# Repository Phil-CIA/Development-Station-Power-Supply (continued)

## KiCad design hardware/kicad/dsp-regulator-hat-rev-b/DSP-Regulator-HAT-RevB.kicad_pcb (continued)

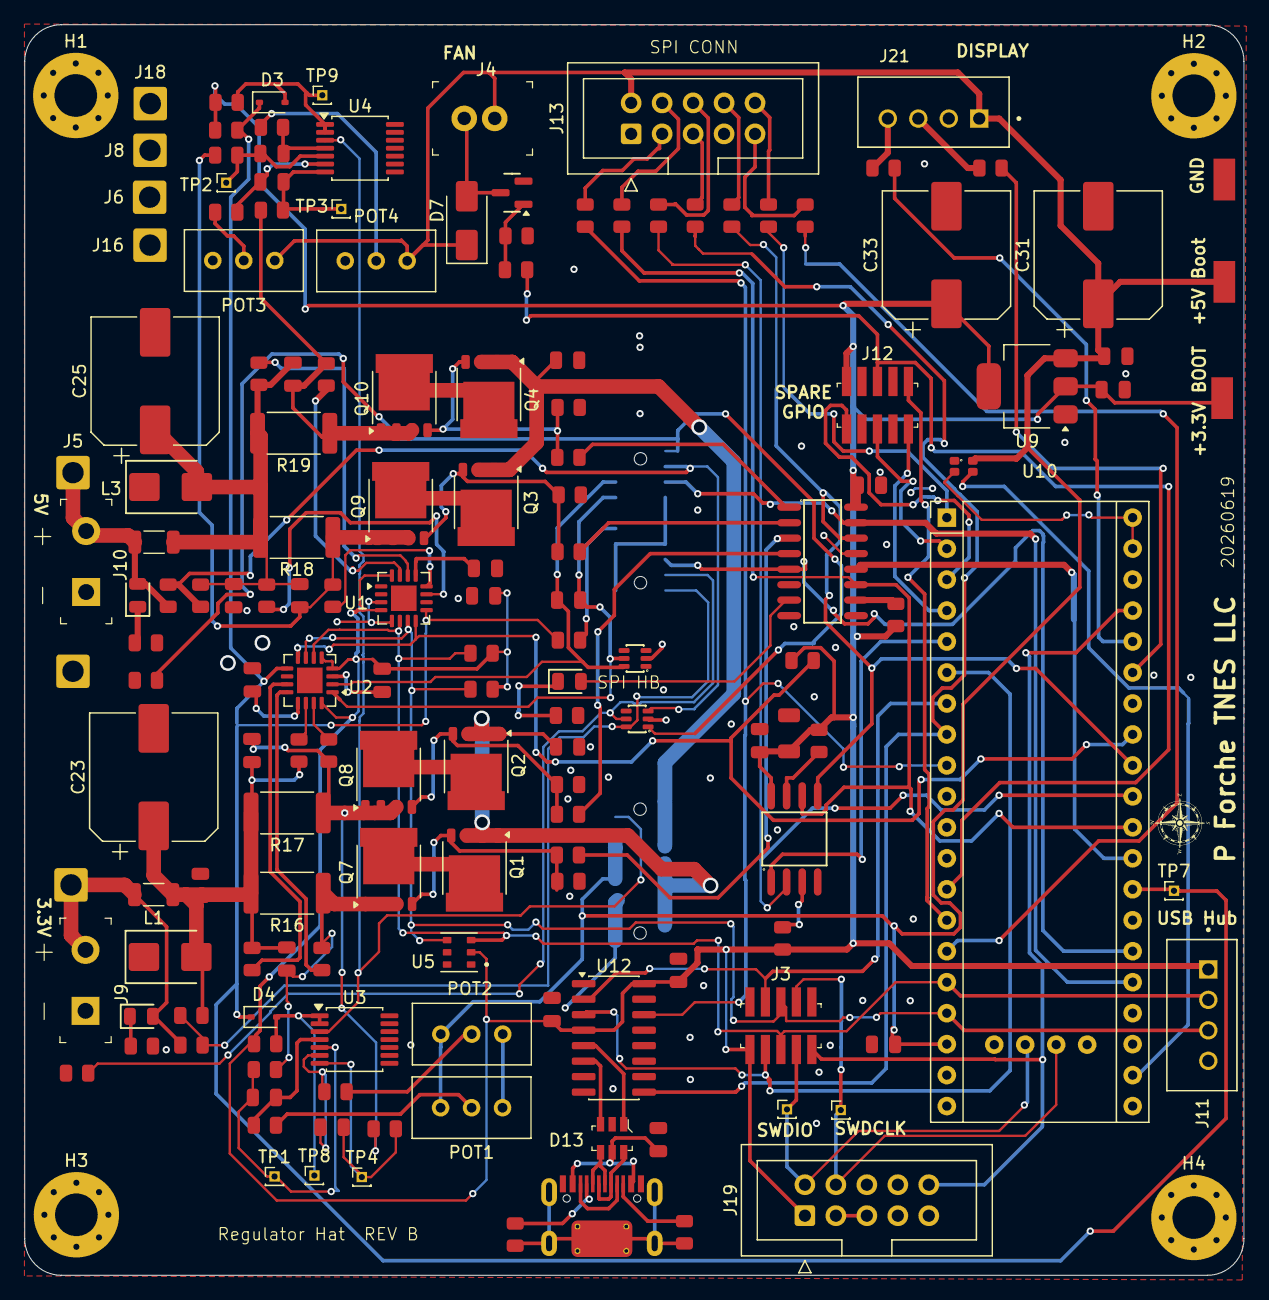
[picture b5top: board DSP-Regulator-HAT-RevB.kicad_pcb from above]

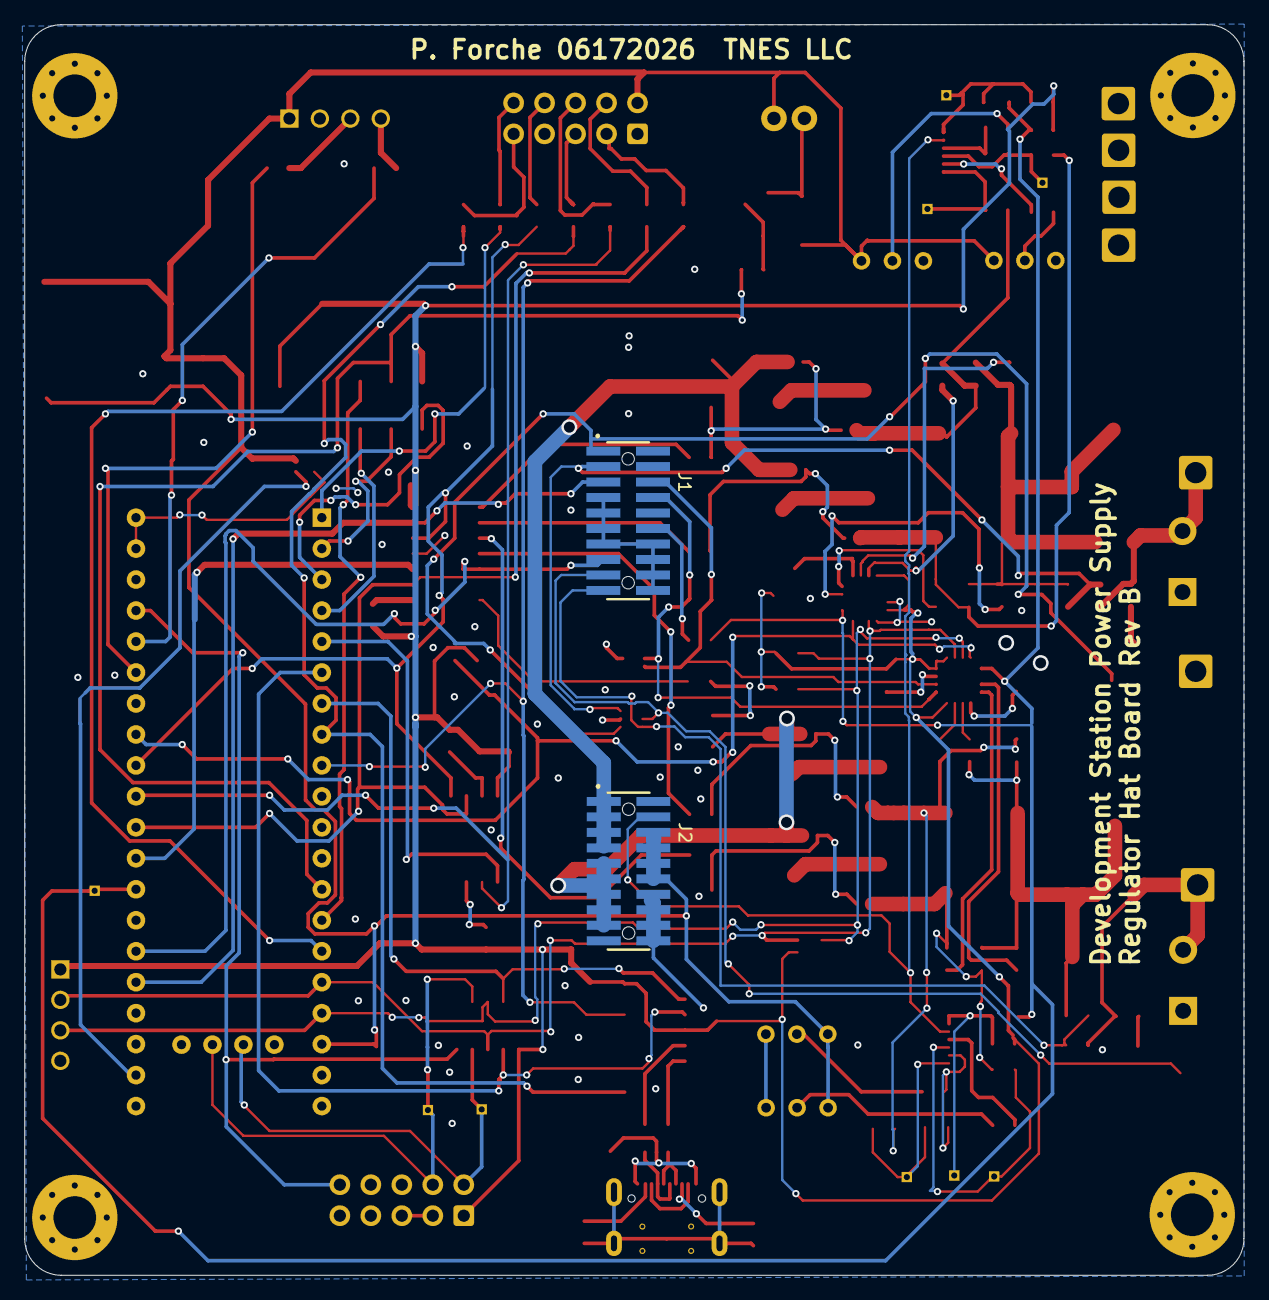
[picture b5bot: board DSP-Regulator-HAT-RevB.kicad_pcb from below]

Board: 2 copper layers, 100.0 x 102.6 mm, 163 parts (2 on the bottom side), 111 nets.

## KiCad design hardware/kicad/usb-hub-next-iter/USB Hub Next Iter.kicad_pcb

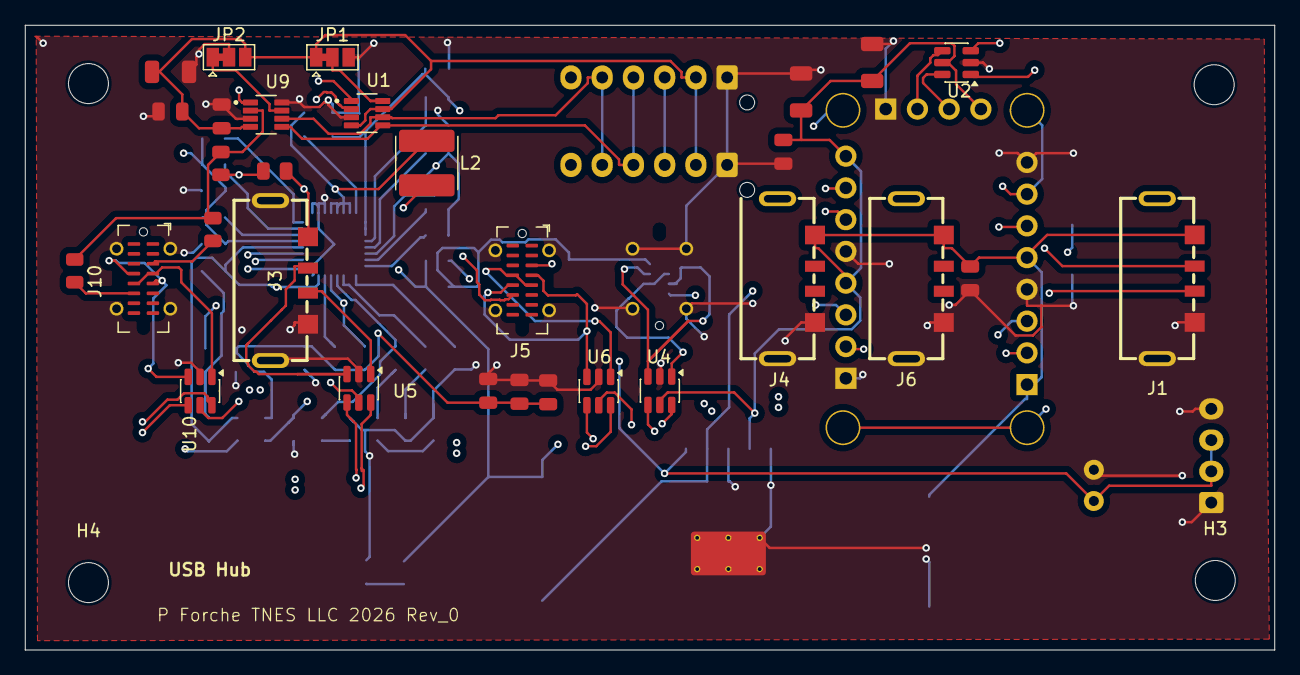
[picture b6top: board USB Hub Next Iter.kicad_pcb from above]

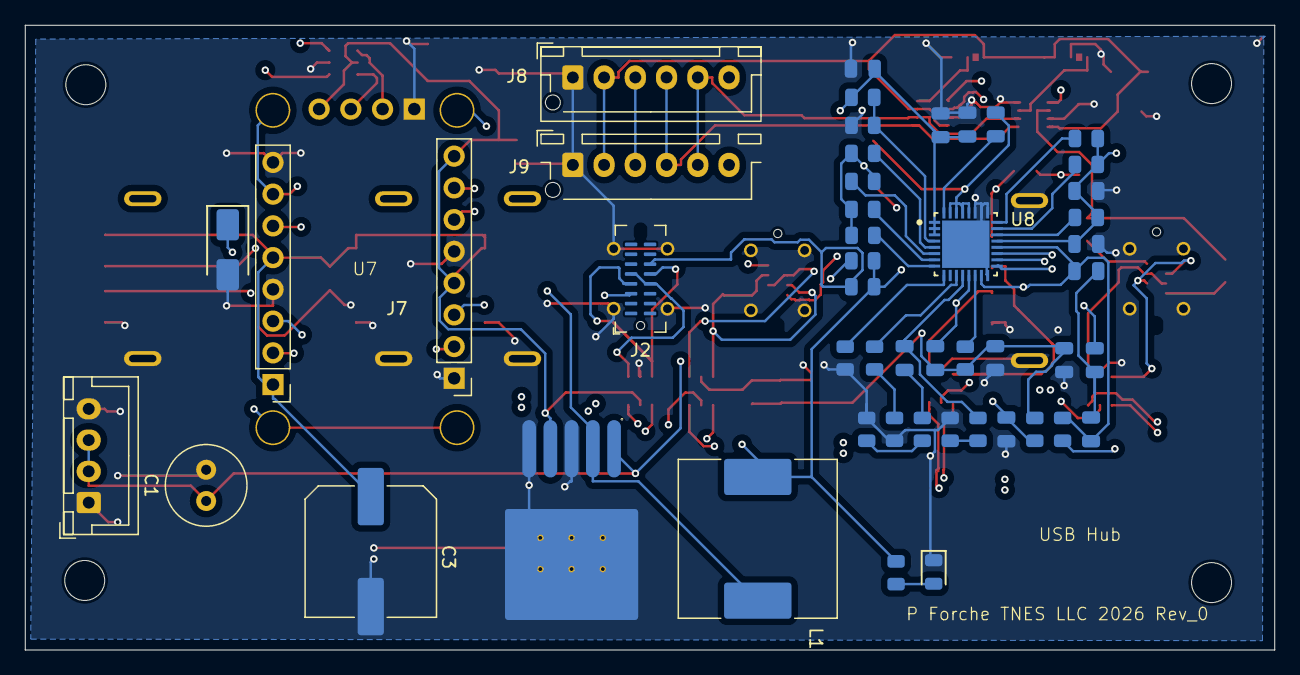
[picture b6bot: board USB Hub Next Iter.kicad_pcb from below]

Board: 4 copper layers, 100.0 x 50.0 mm, 82 parts (48 on the bottom side), 62 nets.

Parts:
C1: 100uF; C_Radial_D6.3mm_H7.0mm_P2.50mm
C2, C5, C7, C11, C17, C18, C19, C20, C21, C26: 100nF; C_0805
C3: 1000uf; C_Elec_10x10.2
C4, C16: 47uF; C_1206
C6, C8, C13: 220nF; C_0805
C9, C10, C12, C14, C15: 22uF; C_0805
C22: 2.2uF; C_0805
C23: 10uF; C_0805
C24: 2.2nF; C_0805
C25: 100uF; C_1206
D1: B360; D_SMA
D2: Green; D_0805
H1, H2, H3, H4: MountingHole; MountingHole_3.2mm_M3
J1, J3, J4, J6: USB_A; USB-A-SMD_916-261B2115S30200
J2, J10: Connector, USB-TYPE-C-16P; USB_C_Receptacle_G-Switch_GT-USB-7051x
J5: Connector, USB-TYPE-C- vert; USB_C_Receptacle_G-Switch_GT-USB-7051x
J7: From 12V supply; JST_XH_B4B-XH-A_1x04_P2.50mm_Vertical
J8, J9: B5B-XH-A_LF__SN_; JST_XH_B6B-XH-AM_1x06_P2.50mm_Vertical
JP1, JP2: SolderJumper_3_Bridged12; SolderJumper-3_P1.3mm_Bridged12_Pad1.0x1.5mm
L1: 100uh; L_Sunlord_SWRB1204S
L2: 3.3uh 4A; L_Coilcraft_1515SQ-47N
R1, R3, R23: 0.01; R_0805
R2: 100Ω; R_0805
R4, R7, R10: 10kΩ; R_0805
R5: 2.7kΩ; R_0805
R6, R9: 1.8kΩ; R_0805
R8: 300Ω; R_0805
R11: 20kΩ; R_0805
R12: 49.9kΩ; R_0805
R13, R21, R22, R25, R26: 5.1kΩ; R_0805
R14, R15, R16, R17, R18, R19, R20: 100kΩ; R_0805
R24: 330Ω; R_0805
U1, U9: INA219; SOT65P280X145-8N
U2, U4, U6, U10: USBLC6; SOT-23-6
U3: LM2576SX; PG-TO-263-5_L10.2-W8.7-P1.70-LS14.4-BR
U5: USBLC6-2SC6; SOT-23-6
U7: ADA_Fruit_CH334F; Adafruit CH334
U8: TPS25830AQCWRHBRQ1; RHB0032AA-IPC_A

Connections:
3v3: C2.2, C25.1, C26.2, J8.2, J9.2, JP1.1 (A), JP2.3 (B), U1.4 (VS), U1.7 (A0), U9.4 (VS)
5V Main Usb: C3.1, C4.1, C5.2, C16.1, C18.2, J1.1 (VBUS), J4.1 (VBUS), J6.1 (VBUS), L1.1, R1.1, R23.2, R24.1, R25.2, R26.2, U1.1 (IN+), U2.5 (VBUS), U3.4 (FB), U4.5 (VBUS), U7.1 (5V_2), U7.5 (5V_4), U7.9 (5V_H), U7.13 (5V_3), U7.17 (5V_1), U9.1 (IN+), U10.5 (VBUS)
+12V: C1.1, C21.1, C23.1, C24.1, J7.2, J7.3, R11.1, U3.1 (VIN), U8.1 (IN), U8.2 (IN), U8.3 (IN)
GND: C1.2, C2.1, C3.2, C4.2, C5.1, C9.2, C10.1, C11.1, C12.2, C14.1, C15.2, C16.2, C18.1, C20.2, C21.2, C22.2, C23.2, C24.2, C25.2, C26.1, D1.2 (A), D2.1, J1.4 (GND), J1.5 (Shield), J2.S1 (SHIELD), J3.4 (GND), J3.5 (Shield), J3.6, J4.4 (GND), J4.5 (Shield), J5.S1 (SHIELD), J6.4 (GND), J6.5 (Shield), J7.1, J7.4, J8.1, J9.1, J10.S1 (SHIELD), JP1.3 (B), JP2.2 (C), R4.2, R7.2, R10.2, R12.1, R13.2, U1.3 (GND), U2.2 (GND), U3.3 (GND), U3.5 (ON#/OFF), U3.6 (TAB), U4.2 (GND), U5.2 (GND), U6.2 (GND), U7.4 (GND_2), U7.8 (GND_4), U7.12 (GND_H), U7.16 (GND_3), U7.20 (GND_1), U8.16 (AGND), U8.25 (PGND), U8.26 (PGND), U8.27 (PGND), U8.33 (Thermal_Pad), U9.3 (GND), U9.8 (A1), U10.2 (GND)
GPIO: J8.3, J9.3
I2C_CLK: J8.4, J9.4, U1.5 (SCL), U9.5 (SCL)
I2C_Data: J8.5, J9.5, U1.6 (SDA), U9.6 (SDA)
unnamed: C7.2, C9.1, C10.2, C12.1, C14.2, C15.1, L2.1, R3.2, R8.1
unnamed: C6.2, C8.2, C13.2
unnamed: C17.1, R6.2
unnamed: C19.1, L2.2, U8.28 (SW), U8.29 (SW), U8.30 (SW), U8.31 (SW)
unnamed: D1.1 (K), L1.2, U3.2 (OUT)
unnamed: D2.2, R24.2
unnamed: J1.3 (D+), U2.1 (I/O1)
unnamed: J1.2 (D-), U2.3 (I/O2)
unnamed: J2.A5 (CC1), R25.1
unnamed: J2.B5 (CC2), R26.1
unnamed: J2.A6 (D+), J2.B6 (D+), U4.3 (I/O2)
unnamed: J2.A7 (D-), J2.B7 (D-), U4.1 (I/O1)
unnamed: J3.3 (D+), U5.1 (I/O1)
unnamed: J3.2 (D-), U5.3 (I/O2)
unnamed: J3.1 (VBUS), R1.2, U1.2 (IN-), U5.5 (VBUS)
unnamed: C6.1, C8.1, J5.A5 (CC1), R2.1, U8.15 (BUS), U8.20 (CC1)
unnamed: C13.1, J5.B5 (CC2), U8.19 (CC2)
unnamed: J5.A6 (D+), J5.B6 (D+), U6.3 (I/O2)
unnamed: J5.A7 (D-), J5.B7 (D-), U6.1 (I/O1)
unnamed: J10.A5 (CC1), R22.2
unnamed: J10.B5 (CC2), R21.2
unnamed: J10.A6 (D+), J10.B6 (D+), U10.1 (I/O1)
unnamed: J10.A7 (D-), J10.B7 (D-), U10.3 (I/O2)
unnamed: JP1.2 (C), U1.8 (A1)
unnamed: JP2.1 (A), U9.7 (A0)
unnamed: R4.1, R5.1
unnamed: R6.1, R7.1
unnamed: R9.1, R10.1
unnamed: R2.2, U6.5 (VBUS)
unnamed: C19.2, U8.32 (BOOT)
unnamed: C7.1, C11.2, R3.1, U8.13 (CSN_OUT)
unnamed: R8.2, U8.14 (CSP)
unnamed: R14.1, U8.5 (CTRL1)
unnamed: R15.1, U8.6 (CTRL2)
unnamed: R19.1, U8.8 (DM_OUT)
unnamed: R20.1, U8.7 (DP_OUT)
unnamed: R11.2, R13.1, U8.4 (EN)
unnamed: R16.1, U8.24 (FAULT_N)
unnamed: C17.2, R9.2, U8.12 (ILIMIT)
unnamed: R5.2, U8.11 (IMON)
unnamed: R17.1, U8.23 (LD_DET_N)
unnamed: R18.1, U8.22 (POL_N)
unnamed: R12.2, U8.9 (RT_SYNC)
unnamed: C20.1, C22.1, R14.2, R15.2, R16.2, R17.2, R18.2, R19.2, R20.2, U8.21 (VCC)
unnamed: R21.1, R22.1, R23.1, U9.2 (IN-)
Port 1_D+: U4.4 (I/O2), U7.18 (+D1_1)
Port 1_D-: U4.6 (I/O1), U7.19 (-D1_1)
Port 2_D+: U7.2 (+D1_2), U10.4 (I/O2)
Port 2_D-: U7.3 (-D1_2), U10.6 (I/O1)
Port 3_D+: U6.4 (I/O2), U7.14 (+D1_3), U8.18 (DP_IN)
Port 3_D-: U6.6 (I/O1), U7.15 (-D1_3), U8.17 (DM_IN)
Port 4_D+: U5.6 (I/O1), U7.6 (+D1_4)
Port 4_D-: U5.4 (I/O2), U7.0 (GND), U7.7 (-D1_4)
Port H_D+: U2.6 (I/O1), U7.10 (+D1_H)
Port H_D-: U2.4 (I/O2), U7.11 (-D1_H)

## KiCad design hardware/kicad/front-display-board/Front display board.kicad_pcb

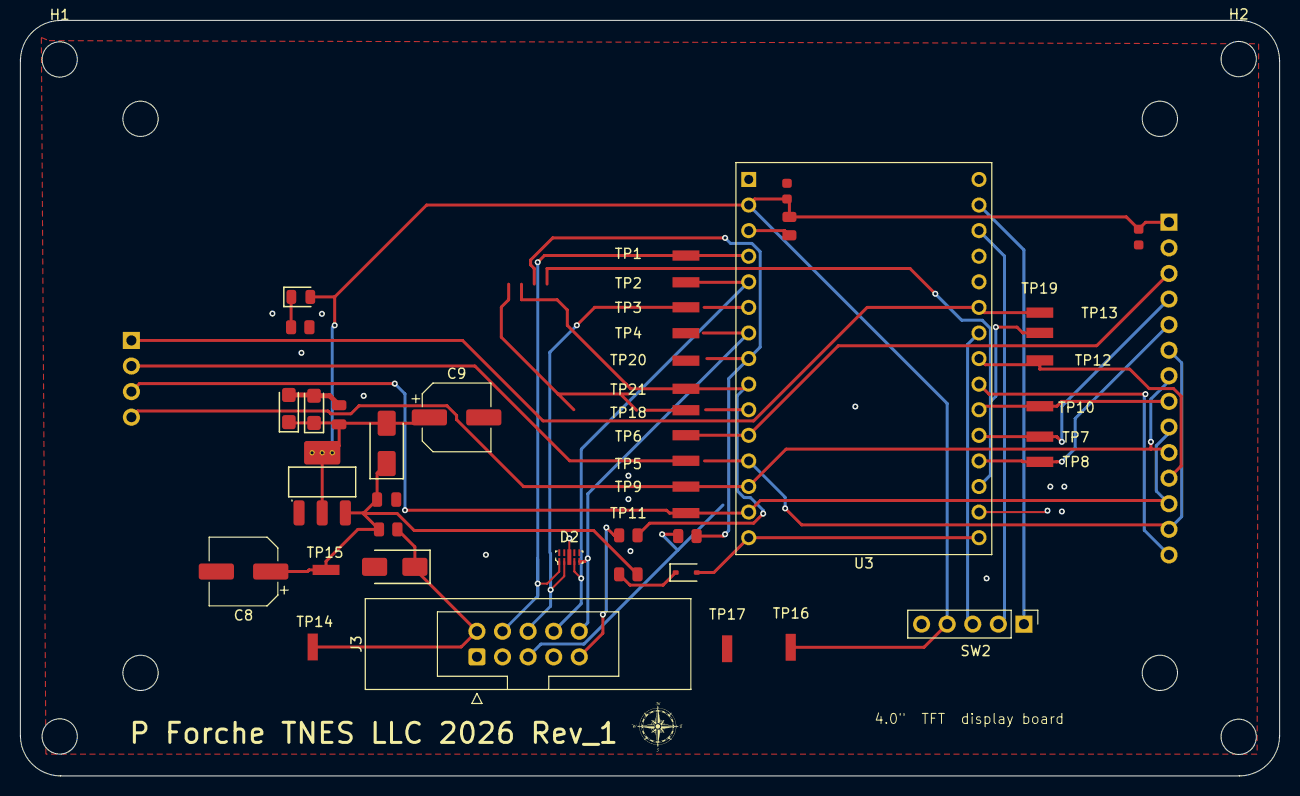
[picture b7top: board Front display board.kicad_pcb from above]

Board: 2 copper layers, 125.0 x 75.0 mm, 50 parts (1 on the bottom side), 31 nets.

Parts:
5mm1: 5mm LOGO
C1, C10: 100nF; C_0603
C4, C5: 10uF; C_CASE-A-3216-18(mm)
C6, C7: 100nF; C_0805
C8, C9: 330uf; CP_Elec_6.3x7.7
D1: M1; D_SMA
D2: RCLAMP0524PATCT; UFDFN-10_2.5x1mm
D3: SMAJ5.0A; D_SMA
D4: Green; D_0805
D5: 1N5819WS; D_SOD-323
F1: PTC RESET FUSE 6V 500mA 0805; R_0805
H1, H2, H3, H4: MountingHole; MountingHole_3.5mm
J3: 2 x 5 IDE; IDC-Header_2x05_P2.54mm_Latch_Vertical
R1: 10kΩ; R_0805
R2: 120Ω; R_0805
R3, R4: 220Ω; R_0805
R5: 0Ω; R_0805
SW2: RotaryEncoder_Switch; PinHeader_1x05_P2.54mm_Vertical
TP1, TP2, TP3, TP4, TP5, TP6, TP7, TP8, TP9, TP10, TP11, TP12, TP13, TP14, TP15, TP16, TP17, TP18, TP19, TP20, TP21: 5015; Test_Point_2.67x1.02mm
U1: DISP 1; Hosyond 4.0 480x320
U2: AMS1117; SOT-223-3_L6.5-W3.4-P2.30-LS7.0-BR
U3: ESP32-C6-DevKitM-Amazon; ESP32-C3-DevKitM-1

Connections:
5 V_IN: D3.1, F1.1, J3.2, TP14.1
+3V3: C1.2, C4.1, C5.1, C6.1, C9.1, C10.2, D1.2, D4.2, R1.1, SW2.4 (+V), TP16.1, U1.1 (VCC), U2.2 (VOUT), U2.4 (VOUT), U3.2 (3V3)
CS: TP6.1, U1.3 (~CS), U3.11 (GPIO10)
D/C: TP8.1, U1.5 (D/~C), U3.19 (GPIO18)
Encoder A: SW2.1 (CLK), U3.29 (GPIO2)
Encoder B: SW2.2 (DT), U3.28 (GPIO3)
Encoder SW: SW2.3 (SW), U3.24 (GPIO23)
GND: C1.1, C4.2, C5.2, C6.2, C7.2, C8.2, C9.2, C10.1, D2.3, D2.8, D3.2, J3.1, J3.3, J3.7, R2.2, SW2.5 (GND), TP17.1, U1.2 (GND), U2.1 (GND), U3.1 (GND), U3.17 (GND), U3.30 (GND)
GPIO1: R4.2, TP21.1, U3.9 (GPIO1)
GPIO8: TP18.1, U3.10 (GPIO8)
GPIO9: TP19.1, U3.18 (GPIO9)
IRQ: U1.14 (T_IRQ), U3.22 (GPIO21)
MISO: TP5.1, U1.6 (MOSI), U1.13 (T_DO), U1.16 (SD_MOSI), U3.12 (GPIO11)
MOSI: TP11.1, U1.9 (MISO), U1.12 (T_DIN), U1.17 (SD_MISO), U3.14 (GPIO13)
unnamed: D4.1, R2.1
unnamed: D5.1, R5.1
unnamed: J3.5, R3.1
unnamed: J3.9, R4.1
unnamed: C7.1, C8.1, D1.1, F1.2, R5.2, TP15.1, U2.3 (VIN)
unnamed: R1.2, U3.3 (EN/RESET)
PMW: TP10.1, U1.8 (LED), U3.21 (GPIO20)
RST: TP7.1, U1.4 (RESET), U3.20 (GPIO19)
RTS/CTS: R3.2, TP20.1, U3.8 (GPIO0)
SCLK: TP9.1, U1.7 (SCK), U1.10 (T_CLK), U1.18 (SD_SCK), U3.13 (GPIO12)
SD card CS: TP13.1, U1.15 (SD_CS), U3.25 (GPIO15)
SPI_CS: D2.5, J3.10, TP4.1, U3.7 (GPIO7)
SPI_MISO: D2.2, J3.6, TP3.1, U3.6 (GPIO6)
SPI_MOSI: D2.4, J3.8, TP2.1, U3.5 (GPIO5)
SPI_SCLK: D2.1, J3.4, TP1.1, U3.4 (GPIO4)
Touch CS: TP12.1, U1.11 (T_~CS), U3.23 (GPIO22)
Vbus: D5.2, U3.15 (5V), U3.16 (5V)

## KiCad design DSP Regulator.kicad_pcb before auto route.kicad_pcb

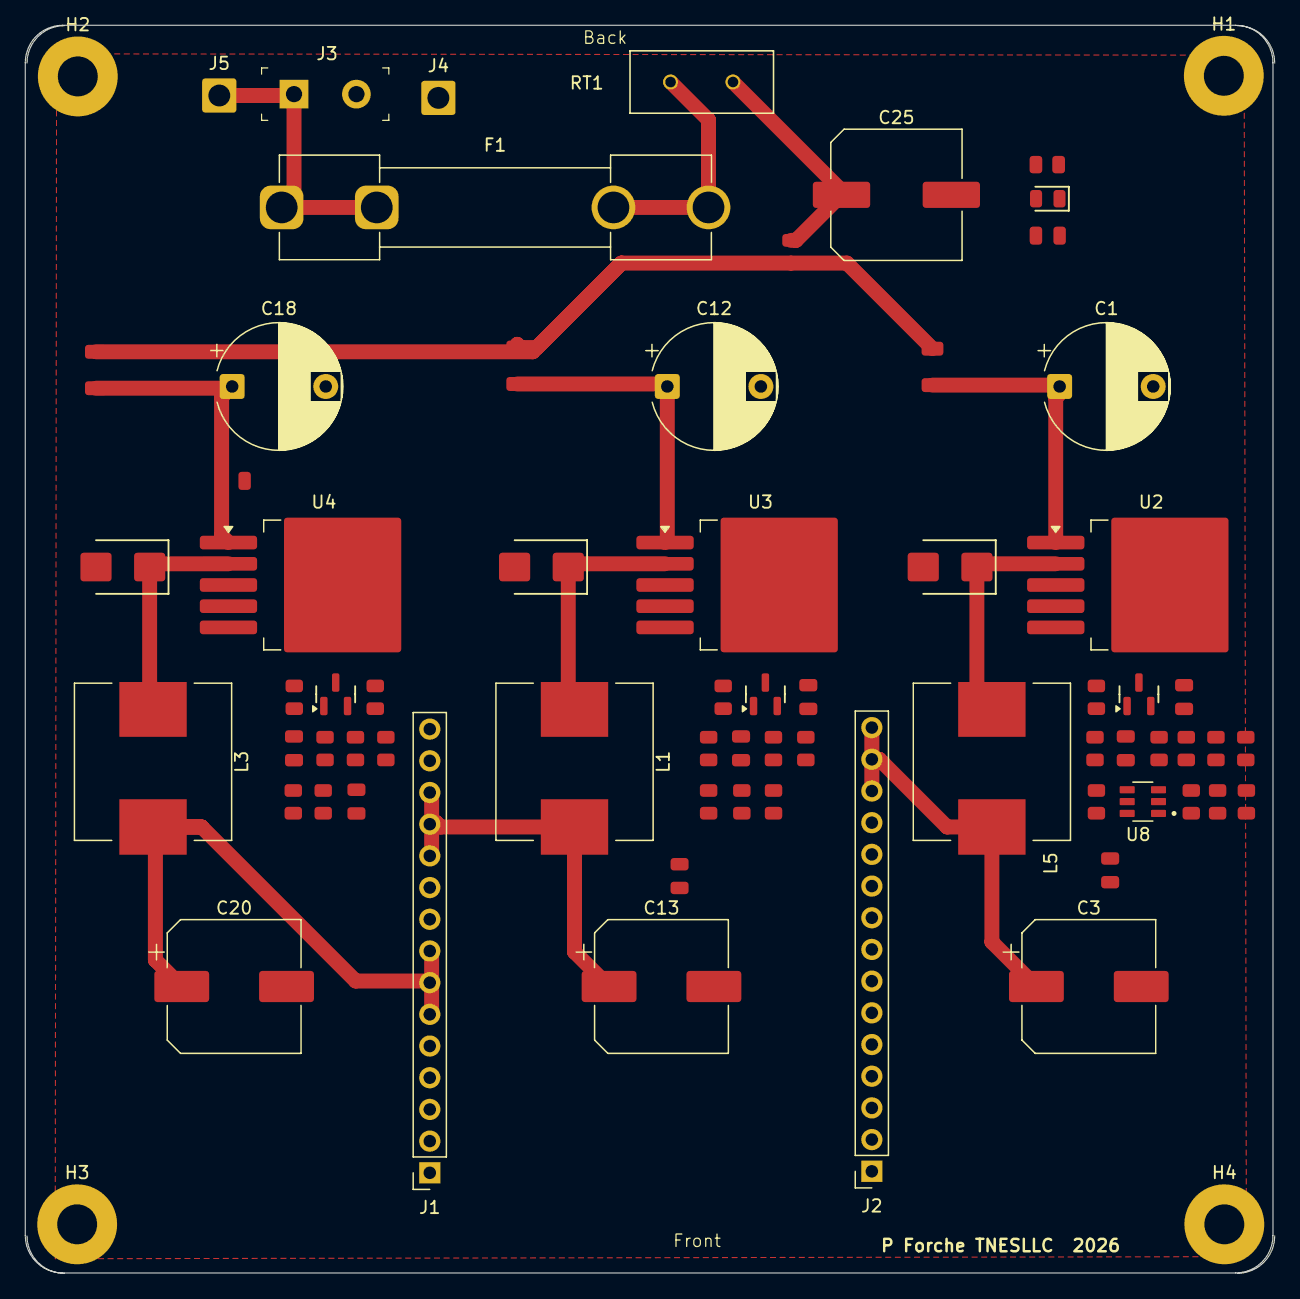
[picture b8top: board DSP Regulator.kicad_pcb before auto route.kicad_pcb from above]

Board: 2 copper layers, 100.0 x 100.0 mm, 71 parts (0 on the bottom side), 42 nets.

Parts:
C1, C12, C18: 470uf 50v; CP_Radial_D10.0mm_P7.50mm
C2, C5, C15, C16, C19, C22: 100nF; C_0805
C3, C13, C20: 330uF 25v; CP_Elec_10x10.5
C7, C11, C21: 100pF; C_0805
C25: 1000uf 25v; C_Elec_10x10.2
C26: 100nf; C_0805
D1, D9, D11: SS54B; D_SMB
D2: Red; D_0805
F1: MDL 5; Fuseholder_Clip-6.3x32mm_Littelfuse_102_Inline_P34.21x7.62m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
H1, H2, H3, H4: MountingHole_Pad; MountingHole_3.2mm_M3_Pad
J1, J2: Conn_01x15_Socket; PinSocket_1x15_P2.54mm_Vertical
J3: 1935161; Terminal_Block_D1.3mm_P5mm
J4, J5: Wire con; SolderWire-1sqmm_1x01_D1.4mm_OD2.7mm
L1, L3, L5: 33uh; L_11.5x10mm_H6mm
Q2, Q3, Q16: BSS138; Q_SOT-23
R1, R4, R5, R6, R64, R65: 100kΩ; R_0805
R2, R19, R24, R41, R63: 100Ω; R_0805
R3, R16, R17: 0Ω; R_1206
R7, R8, R11, R14, R18, R20, R21, R42: 1kΩ; R_0805
R12, R13: 680Ω; R_0805
R22, R43: 2kΩ; R_0805
R23, R26: 0Ω; R_0805
R44: 10mohm; R_0805
RT1: 5 ohms - 4.5amp; Inrush limiter
U2, U3, U4: LM2596S-ADJ; TO-263-5_TabPin3
U8: TS5A3157-DCKR; SOT95P280X145-6N

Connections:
3.3_Select: J2.6, U8.6 (IN)
ISET_MPU_3V3: J1.10, R2.1
ISET_MPU_Channel_3: J2.5, R63.1
+3.3V_Reg: C13.1, C15.1, J1.11, J1.12, J1.13, L1.2
+5V_Control: J2.7, U8.5 (V+)
+5V_reg: C20.1, C22.1, J1.6, J1.7, J1.8, L3.2
+12V: J2.8, R3.1, R16.1, R17.1, R44.2
+V Adj Channel: C3.1, C5.1, J2.13, J2.14, J2.15, L5.2
Feedback 3.3: C7.1, J1.9, R23.2
Feedback 5V: C21.1, J1.4, R22.2
Feedback Adj Channel: C11.1, J2.4, R26.2, R43.2
GND: C1.2, C2.2, C3.2, C5.2, C12.2, C13.2, C15.2, C16.2, C18.2, C19.2, C20.2, C22.2, C25.2, C26.2, D1.2, D9.2, D11.2, H1.1, H2.1, H3.1, H4.1, J1.1, J1.2, J1.3, J2.1, J2.2, J2.3, J3.2, J4.1, R1.2, R4.1, R5.2, R6.1, R7.2, R8.2, R11.2, R18.2, R64.1, R65.2, U2.3 (GND), U3.3 (GND), U4.3 (GND), U8.2 (GND)
ISET_MPU_5V: J1.5, R24.1
Incoming (+): C25.1, C26.1, D2.2, J2.9, R44.1, RT1.2
unnamed: D2.1, R8.1
unnamed: F1.2, RT1.1
unnamed: F1.1, J3.1, J5.1
unnamed: Q2.3 (D), R65.1, U2.5 (~ON/OFF)
unnamed: Q2.1 (G), R63.2, R64.2
unnamed: C1.1, C2.1, Q2.2 (S), R3.2, U2.1 (VIN)
unnamed: Q3.3 (D), R5.1, U4.5 (~ON/OFF)
unnamed: Q3.1 (G), R4.2, R24.2
unnamed: C18.1, C19.1, Q3.2 (S), R17.2, U4.1 (VIN)
unnamed: Q16.3 (D), R1.1, U3.5 (~ON/OFF)
unnamed: Q16.1 (G), R2.2, R6.2
unnamed: C12.1, C16.1, Q16.2 (S), R16.2, U3.1 (VIN)
unnamed: R12.2, R21.1
unnamed: R13.2, R14.1
unnamed: R14.2, R23.1
unnamed: R19.2, R20.1
unnamed: R20.2, R22.1
unnamed: R21.2, R26.1
unnamed: R41.2, R42.1
unnamed: R42.2, R43.1
unnamed: C11.2, R11.1, U2.4 (FB), U8.4 (COM)
unnamed: D1.1, L5.1, U2.2 (OUT)
unnamed: C7.2, R7.1, R13.1, U3.4 (FB)
unnamed: D9.1, L1.1, U3.2 (OUT)
unnamed: C21.2, R18.1, R19.1, U4.4 (FB)
unnamed: D11.1, L3.1, U4.2 (OUT)
unnamed: R41.1, U8.3 (NC)
unnamed: R12.1, U8.1 (NO)

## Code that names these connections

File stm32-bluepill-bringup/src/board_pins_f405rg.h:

#pragma once

#include <Arduino.h>

// Rev-D assignments from docs/HAT_REVD_PIN_AND_SUPPORT_CONTRACT.md.
// USB and C3 pins are reserved candidates; neither interface is enabled by default.
static constexpr uint8_t PIN_DEBUG_RX = PB7;
static constexpr uint8_t PIN_DEBUG_TX = PB6;
static constexpr uint8_t PIN_UDI_RX = PB11;
static constexpr uint8_t PIN_UDI_TX = PB10;
static constexpr uint8_t PIN_C3_UART_RX = PC11;
static constexpr uint8_t PIN_C3_UART_TX = PC10;
static constexpr uint8_t PIN_C3_EN_N = PC0;
static constexpr uint8_t PIN_C3_BOOT_N = PC1;
static constexpr uint8_t PIN_USB_VBUS_SENSE = PA9;
static constexpr uint8_t PIN_USB_DM = PA11;
static constexpr uint8_t PIN_USB_DP = PA12;

static constexpr int8_t PIN_ISET_5V = PA0;
static constexpr int8_t PIN_ISET_3V3 = PA1;
// Rev-D has no CH3 MCU control; PA2 is a free spare.
static constexpr int8_t PIN_ISET_CH3 = -1;
static constexpr int8_t PIN_FAULT_CRITICAL_SUM = -1;
static constexpr uint8_t PIN_AW9523_INT = PC4;
static constexpr uint8_t PIN_STATUS_LED = PC13;
static constexpr uint8_t PIN_FLASH_CS = PA8;
static constexpr uint8_t PIN_SR_LATCH = PA4;
static constexpr uint8_t I2C_SCL_PIN = PB8;
static constexpr uint8_t I2C_SDA_PIN = PB9;

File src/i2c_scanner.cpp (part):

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#include "disp_link.h"

// ----------------------------------------------------------------------------
// Bit-bang I2C master on GPIO5 (SDA) / GPIO6 (SCL).
//
// This bus currently serves bring-up reads for INA3221 devices and the U5
// AHT20 temperature/humidity sensor. Pull-ups are expected externally;
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
// ----------------------------------------------------------------------------
// Shift register control (74HC595 x2 chain — U4 first, U5 daisy-chained)
// SR_Data  → U4 DS      (GPIO3)
// SR_CLK   → U4/U5 SHCP (GPIO4)
// SR_Latch → U4/U5 STCP (GPIO1)
// OE# tied to GND (always output-enabled); MR# pulled HIGH (no reset).
//
// 16-bit value layout after shiftOut16(value):
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//   bits  [7:0] → U4 Q7..Q0
//
// U4 FET gate bit assignments (PMOS: gate LOW = FET ON):
//   bit 0 (U4 Q0): ISET_MPU_5V       → J4 pin 5 (not a load switch)
//   bit 1 (U4 Q1): ESP-GPIO 5V Hi    → R8 → Q2+Q8 gates (5V Low-Range)
//   bit 2 (U4 Q2): ESP-GPIO 5V Low   → R7 → Q1+Q7 gates (5V Hi-Range)
//   bit 3 (U4 Q3): ESP-GPIO 3.3V Hi  → R9 → Q3+Q9 gates (3.3V Hi-Range)
//   bit 4 (U4 Q4): ESP-GPIO 3.3V Low → R10 → Q4+Q10 gates (3.3V Low-Range)
//   bit 5 (U4 Q5): Channel 3 Lo-Rng  → R12 → Q6+Q12 gates (Adj Low-Range)
//   bit 6 (U4 Q6): Channel 3 Hi-Rng  → R11 → Q5+Q11 gates (Adj Hi-Range)
//   bit 7 (U4 Q7): ISET_MPU_3V3      → J4 pin 10 (not a load switch)
//   bits [15:8] (U5 Q0-Q7): channel select / ISET signals → keep 0
// ----------------------------------------------------------------------------
constexpr uint8_t SR_DATA_PIN  = 3;
constexpr uint8_t SR_CLK_PIN   = 4;
constexpr uint8_t SR_LATCH_PIN = 1;
constexpr bool SR_SELF_TEST_ENABLED = false;

// Bitmask for U4 bits 1-6: all six load-switch FET enables
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    digitalWrite(SR_CLK_PIN, LOW);
    delayMicroseconds(2);
  }
  digitalWrite(SR_LATCH_PIN, HIGH);
  delayMicroseconds(2);
  digitalWrite(SR_LATCH_PIN, LOW);
}

void applyShiftRegisterState(const char* reason) {
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  uint8_t scl;
};

// INA3221 sensor bus: bit-bang master on GPIO5/GPIO6 (see top of file).
// HP_I2C0 hardware peripheral is dedicated to disp_link's IDF slave on GPIO0/GPIO7.
constexpr I2cBusCandidate BUS_CANDIDATES[] = {
  {"bus0", INA_SDA, INA_SCL},
};
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  // CURRENT PATH CAVEAT:
  //   CH1/CH2 for all rails are in series with output load-switch MOSFETs
  //   (Q1/Q7 for 5V, Q3/Q9 for 3.3V, Q5/Q11 for Adj Hi, etc.), driven by
  //   the GPIO shift registers (U4/U5). Until those MOSFETs are enabled by
  //   firmware, CH1/CH2 shunt readings will show near-zero even under load.
  //
  // 0x41 CH3 (12V input monitor):
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  // Without this, the 74HC595 power-on state is random and FETs may be OFF.
  pinMode(SR_DATA_PIN,  OUTPUT);
  pinMode(SR_CLK_PIN,   OUTPUT);
  pinMode(SR_LATCH_PIN, OUTPUT);
  digitalWrite(SR_DATA_PIN,  LOW);
  digitalWrite(SR_CLK_PIN,   LOW);
  digitalWrite(SR_LATCH_PIN, LOW);
  enableAllChannels();
  if (SR_SELF_TEST_ENABLED) {
    runShiftRegisterSelfTest();
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  // Bring up the HAT -> CrowPanel display link using UART transport.
  disp_link::begin();

  Serial.println("\nI2C scanner starting (bit-bang on GPIO5/GPIO6 for INA3221 + AHT20)...");
  printCommandHelp();
}

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
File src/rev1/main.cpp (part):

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HatPowerTelemetry hatTelemetry(ina3221);
Preferences prefs;

constexpr uint8_t STATUS_LED_PIN = 2;
constexpr uint8_t MCP4231_CS_PIN = 5;
#if defined(I2C_SDA_GPIO)
constexpr uint8_t I2C_SDA_PIN = I2C_SDA_GPIO;
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constexpr uint8_t INA3221_ADDR_MAX = 0x43;

#if defined(TFT_SCLK)
constexpr int SPI_SCLK_PIN = TFT_SCLK;
#else
constexpr int SPI_SCLK_PIN = 18;
#endif

#if defined(TFT_MISO)
constexpr int SPI_MISO_PIN = TFT_MISO;
#else
constexpr int SPI_MISO_PIN = 19;
#endif

#if defined(TFT_MOSI)
constexpr int SPI_MOSI_PIN = TFT_MOSI;
#else
constexpr int SPI_MOSI_PIN = 23;
#endif

#if defined(MCP4231_SDI_PIN)
constexpr int MCP4231_DATA_PIN = MCP4231_SDI_PIN;
#else
constexpr int MCP4231_DATA_PIN = SPI_MOSI_PIN;
#endif

#if defined(MCP4231_SCK_PIN)
constexpr int MCP4231_CLOCK_PIN = MCP4231_SCK_PIN;
#else
constexpr int MCP4231_CLOCK_PIN = SPI_SCLK_PIN;
#endif

#if defined(TFT_HW_RST)
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constexpr bool RAILADJ_ENABLE_ACTIVE_HIGH = true;

// HMI UART state: per-rail software enable tracking and RailAdj voltage selection.
// These mirror intended hardware state when GPIO pins are not yet assigned.
static bool hmiRailEnabled[3] = {false, false, false};
static bool hmiRailAdjIs5V = true;  // true = 5V selected, false = 3V3 selected

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  Serial.printf("[SPI] TFT_RST=%d\n", TFT_RST);
#endif
  Serial.printf("[SPI] TFT_RESET_PIN=%d polarity=%s\n", TFT_RESET_PIN, TFT_RESET_ACTIVE_LOW ? "active-low" : "active-high");
  Serial.printf("[SPI] BUS SCLK=%d MISO=%d MOSI=%d\n", SPI_SCLK_PIN, SPI_MISO_PIN, SPI_MOSI_PIN);
}

static void runRawSpiBurst(bool verbose) {
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
  digitalWrite(MCP4231_CS_PIN, HIGH);

  if (MCP4231_DATA_PIN == SPI_MISO_PIN) {
    pinMode(MCP4231_DATA_PIN, INPUT_PULLUP);
  }

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  shiftOutByteMsb(0x55);
  digitalWrite(MCP4231_CS_PIN, HIGH);

  if (MCP4231_DATA_PIN == SPI_MISO_PIN) {
    pinMode(MCP4231_DATA_PIN, INPUT_PULLUP);
  }

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#ifdef TOUCH_CS
  pinMode(TOUCH_CS, OUTPUT);
  digitalWrite(TOUCH_CS, HIGH);
  pinMode(SPI_MISO_PIN, INPUT_PULLUP);
  delayMicroseconds(20);

  const int misoIdleHigh = digitalRead(SPI_MISO_PIN);
  digitalWrite(TOUCH_CS, LOW);
  delayMicroseconds(20);
  const int misoWithCsLow = digitalRead(SPI_MISO_PIN);
  digitalWrite(TOUCH_CS, HIGH);

  Serial.printf("[TOUCHBUS] TOUCH_CS=%d MOSI=%d MISO=%d SCLK=%d\n", TOUCH_CS, SPI_MOSI_PIN, SPI_MISO_PIN, SPI_SCLK_PIN);
  Serial.printf("[TOUCHBUS] MISO idle(cs=H)=%d MISO(cs=L)=%d\n", misoIdleHigh, misoWithCsLow);
  Serial.println("[TOUCHBUS] 5 samples (X,Y,Z1,Z2)");

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  digitalWrite(TOUCH_CS, HIGH);
  delayMicroseconds(20);

  Serial.printf("[TOUCHMOSI] CS=%d MOSI=%d MISO=%d SCLK=%d\n", TOUCH_CS, SPI_MOSI_PIN, SPI_MISO_PIN, SPI_SCLK_PIN);
  Serial.println("[TOUCHMOSI] Sending pattern: 0xAA 0x55 0xF0 0x0F x16 with CS low");

  digitalWrite(TOUCH_CS, LOW);
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  digitalWrite(TFT_CS, HIGH);
  delayMicroseconds(20);

  Serial.printf("[TFTMOSI] TFT_CS=%d MOSI=%d MISO=%d SCLK=%d\n", TFT_CS, SPI_MOSI_PIN, SPI_MISO_PIN, SPI_SCLK_PIN);
  Serial.println("[TFTMOSI] Sending pattern: 0xAA 0x55 0xF0 0x0F x16 with TFT_CS low");

  digitalWrite(TFT_CS, LOW);
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      return;
    }
    hmiRailAdjIs5V = (voltTok == "5V");
    // TODO: assert relay GPIO when expander is wired (RAILADJ_VOLT_SEL_PIN)
    Serial.printf("ACK:RAIL_VOLT_SEL rail=RailAdj volt=%s\r\n", hmiRailAdjIs5V ? "5V" : "3V3");
    return;
  }
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  pinMode(I2C_SCL_PIN, INPUT_PULLUP);
  i2cBusRecover();
  Wire.begin(I2C_SDA_PIN, I2C_SCL_PIN, 100000);
  SPI.begin(SPI_SCLK_PIN, SPI_MISO_PIN, SPI_MOSI_PIN);
  SPI.beginTransaction(SPISettings(1000000, MSBFIRST, SPI_MODE0));

  pinMode(STATUS_LED_PIN, OUTPUT);
  digitalWrite(STATUS_LED_PIN, LOW);
  pinMode(MCP4231_CS_PIN, OUTPUT);
  digitalWrite(MCP4231_CS_PIN, HIGH);

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    loopCounter++;

    ledState = !ledState;
    digitalWrite(STATUS_LED_PIN, ledState ? HIGH : LOW);
    if (tftInitialized) {
      drawRuntimeDashboard(now);
    } else if (tftWriteOnlyReady) {
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
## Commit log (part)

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2026-03-24 Initial plan
2026-03-24 Organize repo: move KiCad files, add structure, README, .gitignore
    Agent-Logs-Url: https://github.com/Phil-CIA/Development-Station-Power-Supply/sessions/0bb34265-2691-48e6-b458-3588528c3014
2026-03-25 Update README with current status and pinout details
    Added current status and pinout information for the display board.
2026-03-25 Create pinout documentation for ESP32-C6 display board
    Added authoritative pinout documentation for ESP32-C6 display board, including wiring and firmware pin definitions.
2026-03-26 Initial commit: WorkStation ESP32 PlatformIO project
2026-03-28 Organize new display-board KiCad files into hardware/docs layout
2026-03-28 Organize DSP regulator KiCad projects into hardware/kicad structure
2026-03-28 Organize USB hub KiCad project into hardware/kicad structure
2026-03-28 Add hat rail auto-range and calibration controls
2026-03-28 Persist rail auto-range and calibration config in NVS
2026-03-28 Add project stopping-point handoff to README
2026-03-29 Add per-tap shunt resistance config; fix current measurement for dual-range channels
    - InaTap now carries shuntOhms (HIGH=0.100 Ohm, LOW=0.010 Ohm, 12V=0.010 Ohm defaults)
    - readCurrentmA() uses tap-specific shunt voltage / shuntOhms instead of shared library field
    - setShuntOhms() / shuntOhms() / printShuntConfig() added to HatPowerTelemetry
    - tapRef() private helper for mutable InaTap access
    - NVS schema bumped to v2: shuntOhms[4][3] added to PersistentConfig
    - SHUNT <rail> <range> <ohms>: set per-tap shunt resistor value
2026-03-29 Update default shunt values to BOM (20m/200m/10m) and bump config version
2026-03-29 Add per-rail current-limit protection state machine with NVS persistence
    - Add Iset/Icut/hysteresis config per rail
    - Add modes: LATCH, HICCUP, MONITOR
    - Add trip delay and hiccup retry timers
    - Add runtime CC/trip state tracking and periodic protection update loop
    - Add optional rail enable-pin hooks for future hardware control
    - Add serial commands: CLENABLE, CLSET, CLMODE, CLDELAY, CLSTAT, CLCLEAR
2026-03-29 Add NORMAL/CURRENT_LIMIT operation modes with TFT mode hook
    - Add OperationMode state (NORMAL, CURRENT_LIMIT) with NVS persistence (v5)
    - Add MODE command and include mode in CFGSHOW/HELP
    - Current-limit mode now starts from HIGH range and auto-ranges from measured current
    - Normal mode uses fixed HIGH range and clears active CL runtime state
    - Add tftRequestedOperationMode variable and loop sync hook for panel-driven mode selection
    - Add HatPowerTelemetry::resetActiveRangesToHigh() helper
2026-03-30 Add HANDOFF.md for device handoff
2026-04-12 Add missing front-display and USB hub PCB files
2026-04-12 Add USB hub change tracker and ERC/DRC reports
2026-04-12 Create usb-hub next-iteration workspace and fix 12V net label alias
2026-04-12 Update USB hub tracker with SCH-001 completion
2026-04-12 Revert "Add files via upload"
    This reverts commit 9727bb8fcf1ad0520ca163fc3fe7730c7a9ac76a.
2026-04-12 usb-hub next-iter: add PWR_FLAGs and clear power-pin ERC issues
2026-04-12 usb-hub next-iter: resolve SCH-002 and clear PCB silk overlaps
2026-04-14 usb-hub tracker: correct PCB-002 to resolved, PCB-003 count to 14, revhistory from JSON files
2026-04-14 usb-hub tracker: close all remaining items as Won't Fix (as-built board, no further changes this revision)
2026-04-14 usb-hub tracker: mark superseded — full redesign with new components planned
2026-04-14 usb-hub tracker: files are starting point for redesign and PCB bring-up reference
2026-04-15 Add display project reference folder with official docs and datasheet links
2026-04-15 Update display docs: pivot back to main repo and two-path front-panel plan
2026-04-15 Recharacterize repo docs around current bench-supply and front-panel direction
2026-04-15 Add verified LVGL demo target for ESP32 TFT bring-up
2026-04-16 Add workspace instructions to reduce chat handoffs and keep repo context synced
2026-04-19 Add display_main.cpp for ESP32-C6 front display board initialization
    - Implemented display initialization sequence for ST7796 panel
    - Added color test functionality to verify display operation
    - Configured GPIO pins for display control and backlight management
    - Established communication with the display using Arduino_GFX library
    - Included hardware reset and software reset procedures in setup
    - Display shows "Ready - waiting for host" after initialization
2026-04-19 Document display-board breakpoint and preserve minimal C6 TFT baseline
    # Conflicts:
    # .gitignore
2026-04-23 Add CMD: HMI UART command handler stubs
    - handleHmiCommand(): parses CMD:<ACTION> key=value frames (uppercased)
    - CMD:READ_STATUS: returns state/mode/per-rail V+I/r2_sel, fault code
    - CMD:RAIL_ENABLE: sets hmiRailEnabled[], calls setRailOutputEnabled()
    - CMD:RAIL_VOLT_SEL: guards rail-on interlock, updates hmiRailAdjIs5V
    - CMD:SET_MODE: calls applyOperationMode()
    - CMD:RESET: clears all CL trip state, rejects when not in fault
2026-04-28 Checkpoint: display bring-up docs and firmware updates
2026-05-14 docs: add 2026-05-14 handoff and split priorities
2026-05-16 Add development-station handoff templates
2026-05-19 docs: align handoffs and add Rev-B schematic population checklist
2026-05-19 docs: log schematic population batch B1 verification
2026-05-19 docs: log RB-003 mapping check and correct source-net snapshot
2026-05-19 docs: log critical Batch 3 finding - ON/OFF pulls are 10k not 100k
2026-05-21 docs: add rev-c pre-order handoffs and footprint measurement gate
2026-05-23 docs: closeout handoff and connector planning updates
2026-05-24 Add power telemetry mapping for Hat-board using INA3221
    - Introduced `HatPowerTelemetry` class to manage power telemetry for various rails.
    - Defined enums for `HatRail` and `HatRange` to represent different power rails and measurement ranges.
    - Created structures for `InaTap`, `RailMapping`, `RailMeasurement`, and `RailCalibration` to encapsulate relevant data.
    - Implemented methods for setting INA addresses, reading measurements, applying calibration, and printing configurations.
    - Added support for automatic range switching based on current thresholds.
    - Included methods for resetting calibration and active ranges.
2026-05-24 Add HatPowerTelemetry class for power telemetry management
    - Introduced HatPowerTelemetry class to manage power telemetry for various rails.
    - Defined enums for HatRail and HatRange to represent different power rails and measurement ranges.
    - Created structures for InaTap, RailMapping, RailMeasurement, and RailCalibration to encapsulate relevant data.
    - Implemented methods for setting INA addresses, reading measurements, applying calibration, and managing shunt configurations.
    - Added functionality for automatic range switching based on current thresholds.
    - Included methods for printing telemetry mapping and calibration data for debugging purposes.
2026-05-27 2026-05-27: Display interface complete + session docs cleanup
    HAT Rev-B schematic:
    - Added J21 (JST XH B4B-XH-A 4-pin LCSC C144394) as display UART connector
    - Removed I2C_1: deleted J14/J15 headers; repurposed R78/R79 to 33-ohm UART series resistors
    - PB10 (U10 pin 35) -> DISP_UART_TX, PB11 (pin 36) -> DISP_UART_RX (USART3)
    - ERC: 0 errors / 0 warnings; netlist re-exported 07:48:36
    - verify-connector-contract.ps1 -Mode reduced: 18/18 PASS
2026-05-28 Refactor code structure for improved readability and maintainability
2026-05-29 hw(kicad): add autosave files for DSP Regulator HAT and Rev B
2026-05-31 firmware: enable C6<->CrowPanel UART link and display bring-up baseline
2026-05-31 docs: add May handoffs, tracker updates, and map captures
2026-06-05 Closeout: checkpoint display bring-up, guard scripts, and docs
